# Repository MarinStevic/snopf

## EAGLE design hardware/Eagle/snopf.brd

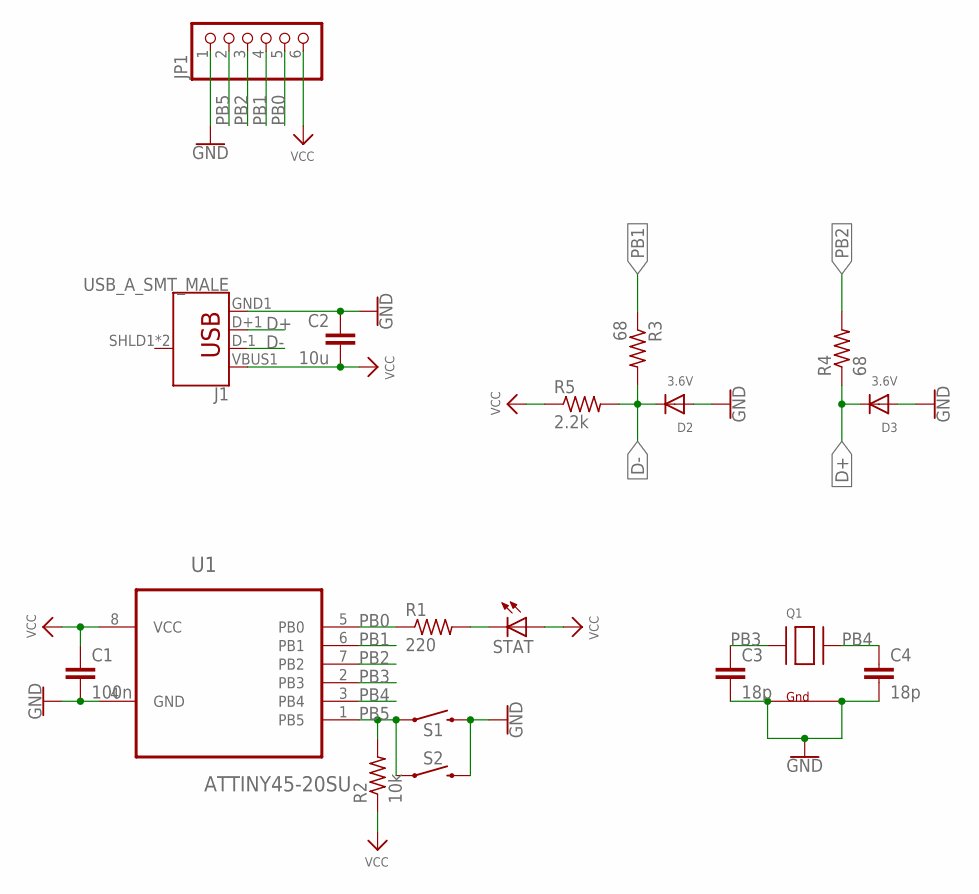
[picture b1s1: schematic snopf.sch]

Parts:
C1: 100n; C0603
C2: 10u; C0603
C3, C4: 18p; C0603
D2, D3: 3.6V; SOD-123
J1: USB_A_SMT_MALE; USB-A-SMT-MALE
JP1: PINHD-1X6CLEAN; 1X06-CLEAN
Q1: XTAL-4-3225; NX3225
R1: 220; R0603
R2: 10k; R0603
R3, R4: 68; R0603
R5: 2.2k; R0603
S1: MOMENTARY-SWITCH-SPST-SMD-12MM; TACTILE_SWITCH_SMD_12MM
S2: MOMENTARY-SWITCH-SPST-SMD-5.2-REDUNDANT; TACTILE_SWITCH_SMD_5.2MM
STAT: LEDCHIPLED_0603; CHIPLED_0603
U1: ATTINY45-20SU; SOIC127P798X216-8N

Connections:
D+: D3.C, J1.D+1 (D+), R4.1
D-: D2.C, J1.D-1 (D-), R3.2, R5.2
GND: C1.2, C2.1, C3.2, C4.2, D2.A, D3.A, J1.GND1 (GND), JP1.1, Q1.2 (G2), Q1.4 (G1), S1.3 (2), S2.3 (2), S2.4 (2), U1.4 (GND)
unnamed: R1.2, STAT.C
PB0: JP1.5, R1.1, U1.5 (PB0)
PB1: JP1.4, R3.1, U1.6 (PB1)
PB2: JP1.3, R4.2, U1.7 (PB2)
PB3: C3.1, Q1.1 (X1), U1.2 (PB3)
PB4: C4.1, Q1.3 (X2), U1.3 (PB4)
PB5: JP1.2, R2.2, S1.1, S2.1, S2.2 (1), U1.1 (PB5)
VCC: C1.1, C2.2, J1.VBUS1 (VBUS), JP1.6, R2.1, R5.1, STAT.A, U1.8 (VCC)

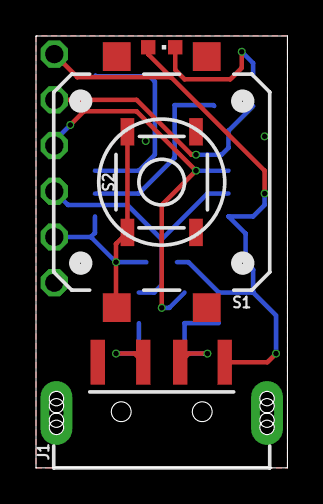
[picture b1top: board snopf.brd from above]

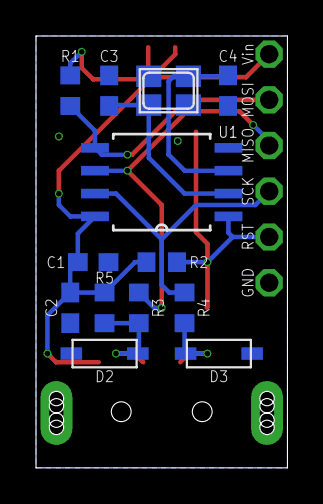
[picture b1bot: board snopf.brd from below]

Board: 2 copper layers, 14.0 x 24.0 mm, 18 parts (13 on the bottom side), 11 nets.

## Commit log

2020-05-15 add accounts table and biometric authentication to android app
    Accounts table:
    -data about accounts is stored in JSON format in InternalStorage/Android/data/com.snopf.snopf/files/AccountsTable.json
    -the data is stored differently from the way it is stored using snopf_cmd and snopf_manager so the two aren't interchangeable
    -if you delete the app the accounts table will be deleted
    -you can see all the accounts stored by going to the menu in the upper right corner
    -if you try to add an account with the same parameters it won't be added to the list
2020-06-16 fix password input not hidden
2020-06-19 add Eagle files
    - this is a different version from the original
    - it has a header for programming

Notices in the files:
parts and their libraries:
SparkFun-Connectors: Licensing: Creative Commons ShareAlike 4.0 International - https://creativecommons.org/licenses/by-sa/4.0
